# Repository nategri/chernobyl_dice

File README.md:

# Chernobyl Dice

<p align="center"><i>In this clip the Chernobyl Dice set to continuously generate numbers in the range [1,26]. You
can check out a longer YouTube clip showing various modes of here: https://youtu.be/8uue9Aae9ss</i></p>

## Introduction

#### Description

The Chernobyl Dice is a quantum random number generator [0] that uses nuclear decays from a weakly radioactive sample
as a source of entropy. It consists of four primary components:

* An Arduino Nano microcontroller
* A Geiger counter
* Six uranium glass marbles
* Nixie tube display

Geiger counter events ("clicks") are converted into random bits using the following algorithm:

1. In a ring buffer, for each millisecond record either a 0 or a 1, depending on whether or not a Geiger event occurred
2. Perform an initial de-bias of this 0-dominated stream using von Neumann's method [0]
3. Further de-bias by XOR-ing bits generated in the previous step with the mod2 of elapsed 4 microsecond intervals since
since the device was powered on

The uranium glass sample is illuminated by an array of ultraviolet LEDs at each Geiger event, which makes them
fluoresce bright green. This has nothing to do with the radioactivity of the sample, but it does, however, *look
really cool*.

#### Operation

The device has three modes of operations, which can be selected via the rotary switch:

*Clock Mode*

Displays the current time, with the Geiger board unpowered. The time can be set by flipping the toggle switches on and off
(the '16' toggle increments the hour, the '8' toggle increments 10 minutes, the '4' toggle increments 1 minute, and the
'1' toggle resets the seconds).

*Streaming Mode*

Repeatedly generates random numbers of a size specified by the toggles (or random bytes from 0-255 if no toggles are set). Numbers
generated in this mode are transmitted over serial via USB. This mode also has a "turbo" setting to facilitate statistical testing,
which can be enabled by holding down the pushbutton. When "turbo" is enabled bit generation will be indicated by LEDs in the
display, and the Geiger "clicks" will be silent.

*Dice Mode*

In dice mode random number generation is initiated via the pushbutton, and the size of the random number to be generated is set
by the sum of the toggled switches (no switches are set the device will generate random byte in the range 0-255). Press
once to generate the number, and once again to clear the display. The size of the number to be generated is displayed in
blinking digits.

## Statistical Performance

Further testing is required to confirm the consistency of results, but currently the Chernobyl Dice is capable of generating a
1.5+ megabit file that passes [a Python implementation](https://github.com/dj-on-github/sp800_22_tests) of the NIST statistical
test suite [1]. This means the Chernolbyl Dice is likely a *very* fair dice.

```
SUMMARY
-------
monobit_test                             0.279698915238     PASS
frequency_within_block_test              0.404035783453     PASS
runs_test                                0.0688862287393    PASS
longest_run_ones_in_a_block_test         0.959135200804     PASS
binary_matrix_rank_test                  0.532456847429     PASS
dft_test                                 0.000155432528185  FAIL
non_overlapping_template_matching_test   0.999998184707     PASS
overlapping_template_matching_test       0.55898054206      PASS
maurers_universal_test                   0.224223569722     PASS
linear_complexity_test                   0.672504584189     PASS
serial_test                              0.424389760139     PASS
approximate_entropy_test                 0.425255814114     PASS
cumulative_sums_test                     0.348500456103     PASS
random_excursion_test                    0.0753308212732    PASS
random_excursion_variant_test            0.207160448911     PASS
```

```
SUMMARY
-------
monobit_test                             0.105735760191     PASS
frequency_within_block_test              0.436487225319     PASS
runs_test                                0.648059641506     PASS
longest_run_ones_in_a_block_test         0.184787158208     PASS
binary_matrix_rank_test                  0.310400523277     PASS
dft_test                                 0.156504142574     PASS
non_overlapping_template_matching_test   1.00000015958      PASS
overlapping_template_matching_test       0.629208901365     PASS
maurers_universal_test                   0.938296605093     PASS
linear_complexity_test                   0.0880093291441    PASS
serial_test                              0.131826155057     PASS
approximate_entropy_test                 0.137234909215     PASS
cumulative_sums_test                     0.112328349057     PASS
random_excursion_test                    0.17207234069      PASS
random_excursion_variant_test            0.299605480729     PASS
```
<p align="center"><i>Statistical test suite results for two 212667 byte random binary sequences ('rand.binary.1' and 'rand.binary.2')
generated by device. EXPERTS NOTE: The last two tests of the first sequence generate the message: 'J too small
(J=181 < 500) for result to be reliable' so these tests may be ignored for that dataset.</i></p>

The directory `statistical_testing` contains some utilities for assessing and gathering data from the device, including sample
random binary data files, `rand.binary.1` and `rand.binary.2`.

## CAD Drawing

A Fusion 360 CAD drawing of the device can be viewed and downloaded at this URL:

https://a360.co/2OeFT1n

Thanks to the following GrabCAD users for their models:
* [Alex](https://grabcad.com/alex-160) (Nixie tube)
* [Mike Smith](https://grabcad.com/mike.smith-208) (Arduino Nano)
* [Dragos Ionescu](https://grabcad.com/dragos.ionescu-2) (Various pin headers)

## Overview and Parts List

*WARNING: These instructions and resources are not polished and are somewhat untested. This is a project for advanced makers, and
you should fully expect to have a bit of an adventure while building your own Chernobyl Dice! That said: Shoot me a message if
you run into trouble, and I'll try to help you out and improve the instructions as well.*

Here's a rough outline of the steps required for assembly:

1. Print or fabricate the following custom parts from files in the GitHub repository
    * Enclosure (using 3D printer or 3D printing service)
    * Logic, Nixie Display, and Control Panel Custom PCBs (using a board fabrication service such as OSHPark)
    * Stainless steel front panel (using a service such as OSHCut)
    * Acrylic back panel (using a service such as Sculpeo)
2. Order other components (see URLs in the parts list)
3. Embed brass standoffs into enclosure (this is how front and back panels and custom PCBs will be mounted)
    * TIPS
      * A single drop of cyanocrylate (superglue) should be placed in the standoff holes in the enclosure before they are pressed
        in (the tip of a Phillips head screw driver works well for this task)
      * If the tops some holes came out of the printer a bit distorted then they can be widened easily by twisting a largish
        Phillips head screwdriver in them until the top of the hole is wide enough.

4. Assemble custom PCBs and 'exixe' nixie tube driver boards using build photos as a guide
    * TIPS
      * The female headers on the Nixie Display Board for the nixie tube driver PCBs can be assembled using only four long female
        header strips (e.g. there's no need to separately attach sixteen 7-pin female headers---see photos)
      * The "CS" 8-pin male header is a currently a tight fit, so you will probably need to use needle noise pliers to push the pins
        through the board
      * For the control panel PCB you can temporarily mount the toggle switches in the front panel and then press the PCB on top of
        the back of the switches to ensure good alignment---you can then pull the whole board-and-toggle assembly off of the front
        panel to solder it, or even solder it in place and then pull it off
      * The file 'nixie_holder.stl' is a provided as a useful place to rest the nixie tube while soldering them to the 'exixe' driver
        boards
5. Attach the acrylic back panel and panel mount USB cable to the rear of the enclosure
6. Mount custom PCBs inside enclosure and perform wiring (see wiring schematic and build photos)
7. Partially dis-assemble rotary switch to attach it to the "lock plate" (lock_plate.stl)
8. Perform any necessary finishing to the stainless steel front panel
    * TIPS
      * Some mounting holes for toggles and switches may need to be widened (use a round file for this)
      * Surface finish of a laser cut part can be improved by sanding *with the grain* using ~300 grit sandpaper (test on the back
        side first)
9. Mount toggle-and-PCB assembly, LED-with-holder assemblies, rotary-switch-and-lock-plate assembly, and pushbutton on front panel
    * TIP
      * While attaching the LED to the holder, apply a drop of cyanocrylate (superglue) to prevent the LED from falling out of the
        front of the holder
10. Perform wiring of the control panel (see wiring schematic and build photos)
11. Fit the eight nixie display driver boards into the female headers of the Nixie Display Board
12. Wire the Control Panel to the Logic Board
13. Mount the front panel to the enclosure, taking care to insure that the hole in the rotary switch lock plate lines up with the
    upper-left standoff on the front of the radioactive sample holder

**Standoff Size Guide**

| Location | Standoff Length | Type |
| --- | --- | --- |
| Rear of enclosure | 10 mm | Female-Female |
| Front of enclosure | 10 mm | Female-Female |
| Nixie Display Board mount | 40 mm | Female-Female |
| Logic Board mount | 20 mm | Female-Female|
| Logic Board-to-Geiger Board | 30 mm | Male-Female |
| Geiger Board-to-Bottom of Uranium Sample Box | 15 mm | Male-Female |
| Bottom of Uranium Sample Box-to-Top of Uranium Sample Box | 6 mm | Male-Female |
| Top of Uranium Sample Box-to-Front Panel | 6 mm | Male-Female |

NOTE: For large internal standoff distances (e.g. the Nixie Display mount) two standoffs can be stacked to achieve
the desired distance.

## Wiring Diagram

<p align="center"><i>How connect the internal wiring of the Chernobyl Dice.</i></p>

## Build Photos

**Enclosure with Standoffs Inserted**

<p align="center"><i>
You can ignore the white breadboards on the left of the enclosure. These assisted in an earlier iteration of the
project and are not needed for assembly.
<a href="https://raw.githubusercontent.com/nategri/chernobyl_dice/master/images/build/large/1.JPG">Click here</a>
for larger photo.
</i></p>

<br><br><br>

**Logic Board Mounted**

<p align="center"><i>
Note the wires for UV LED array are run beneath the logic board.
<a href="https://raw.githubusercontent.com/nategri/chernobyl_dice/master/images/build/large/2.JPG">Click here</a>
for larger photo.
</i></p>

<br><br><br>

**Nixie Display Board Wiring**

<p align="center"><i>
<a href="https://raw.githubusercontent.com/nategri/chernobyl_dice/master/images/build/large/3.JPG">Click here</a>
for larger photo.
</i></p>

<br><br><br>

**Nixie Display Board Mounted and Logic Board Wiring**

<p align="center"><i>
<a href="https://raw.githubusercontent.com/nategri/chernobyl_dice/master/images/build/large/4.JPG">Click here</a>
for larger photo.
</i></p>

<br><br><br>

**Geiger Board Mounted**

<p align="center"><i>
NOTE: You must pull the JMP2 jumper near the center of the Geiger board (this turns off the built-in speaker of the
board---we want these clicks to be optional and controlled by firmware instead).
<a href="https://raw.githubusercontent.com/nategri/chernobyl_dice/master/images/build/large/5.JPG">Click here</a>
for larger photo.
</i></p>

<br><br><br>

**Uranium Sample Holder Lower Half Detail**

<p align="center"><i>
UV LEDs and piezo speaker are glued mounted into place using cyanocrylate (superglue) adhesive. Uranium glass
marbles will be held in place mechanically when the top half is mounted.
<a href="https://raw.githubusercontent.com/nategri/chernobyl_dice/master/images/build/large/6.JPG">Click here</a>
for larger photo.
</i></p>

<br><br><br>

**Uranium Sample Holder Lower Half Mounted**

<p align="center"><i>
The middle standoff is attached on the underside with a nut.
<a href="https://raw.githubusercontent.com/nategri/chernobyl_dice/master/images/build/large/7.JPG">Click here</a>
for larger photo.
</i></p>

<br><br><br>

**Uranium Sample Holder Top Half Mounted**

<p align="center"><i>
<a href="https://raw.githubusercontent.com/nategri/chernobyl_dice/master/images/build/large/8.JPG">Click here</a>
for larger photo.
</i></p>

<br><br><br>

**Control Panel Board Wired**

<p align="center"><i>
<a href="https://raw.githubusercontent.com/nategri/chernobyl_dice/master/images/build/large/9.JPG">Click here</a>
for larger photo.
</i></p>

<br><br><br>

**Control Panel Board Wiring Detail**

<p align="center"><i>
<a href="https://raw.githubusercontent.com/nategri/chernobyl_dice/master/images/build/large/10.JPG">Click here</a>
for larger photo.
</i></p>

## Acknowledgements

Many thanks to Emily Velasco ([@MLE_Online](https://twitter.com/MLE_Online)) for advice on stainless steel surface sanding,
and for generally being enthusiastic as heck about this project.

## References

[0] "Quantum Random Number Generators." M. Herrero-Collantes and J. C. Garcia-Escartin.
https://arxiv.org/abs/1604.03304

[1] "A Statistical Test Suite for Random and Pseudorandom Number Generators for Cryptographic Applications."
https://csrc.nist.gov/publications/detail/sp/800-22/rev-1a/final

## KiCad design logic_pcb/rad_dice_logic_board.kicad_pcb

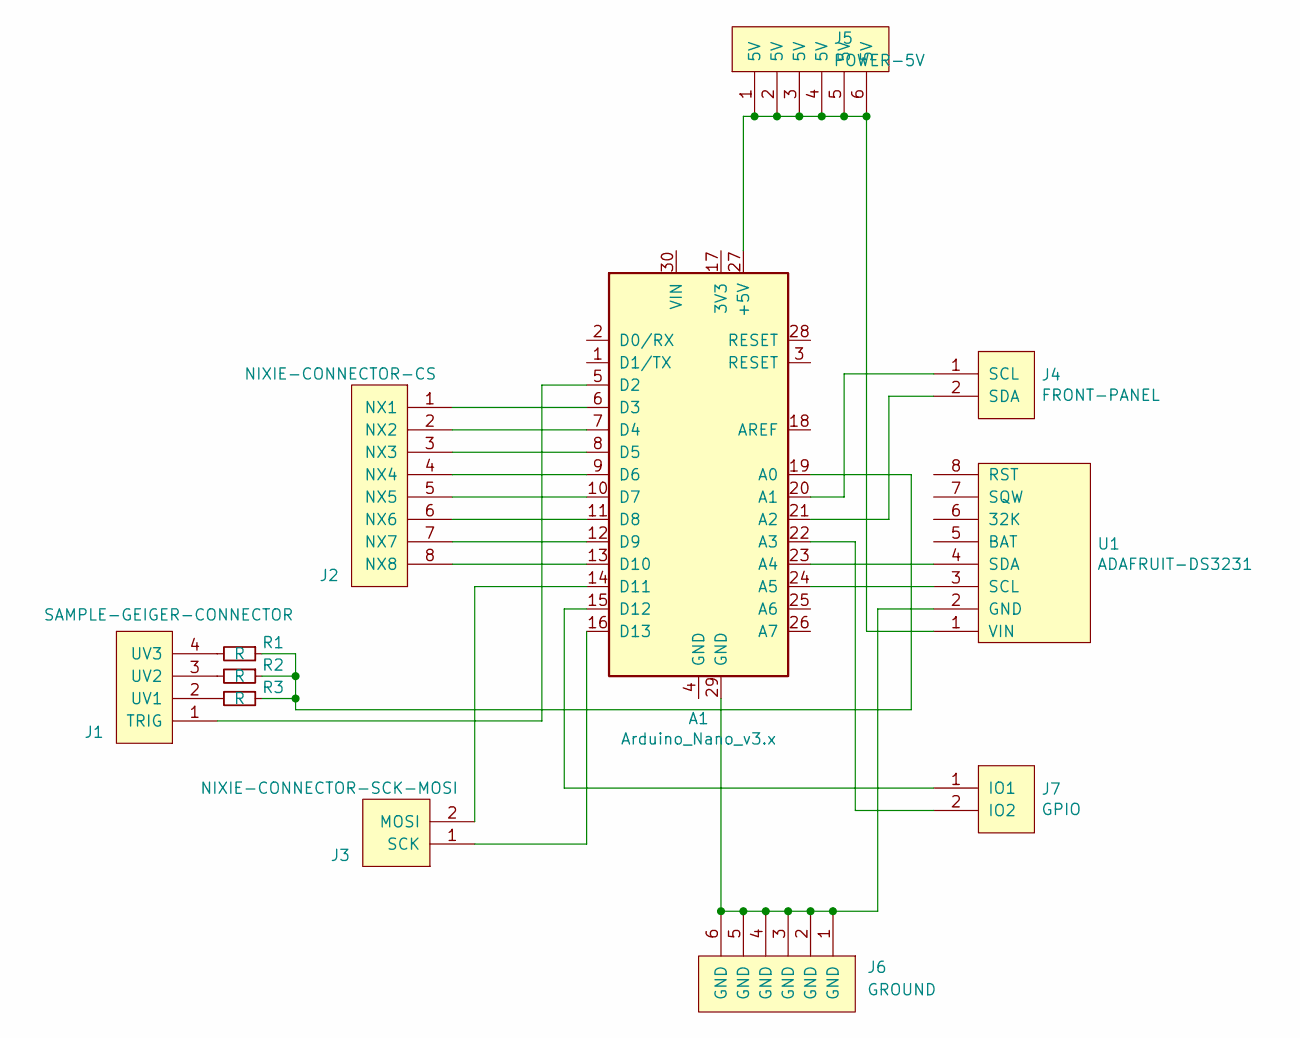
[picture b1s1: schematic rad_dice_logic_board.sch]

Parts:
A1: Arduino_Nano_v3.x; Arduino_Nano
J1: SAMPLE-GEIGER-CONNECTOR; Pin_Header_Angled_1x04_Pitch2.54mm
J2: NIXIE-CONNECTOR-CS; Pin_Header_Angled_1x08_Pitch2.54mm
J3: NIXIE-CONNECTOR-SCK-MOSI; Pin_Header_Angled_1x02_Pitch2.54mm
J4: FRONT-PANEL; Pin_Header_Angled_1x02_Pitch2.54mm
J5: POWER-5V; Pin_Header_Angled_1x06_Pitch2.54mm
J6: GROUND; Pin_Header_Angled_1x06_Pitch2.54mm
J7: GPIO; Pin_Header_Angled_1x02_Pitch2.54mm
R1, R2, R3: R; R_Axial_DIN0207_L6.3mm_D2.5mm_P10.16mm_Horizontal
U1: ADAFRUIT-DS3231

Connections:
unnamed: A1.5 (D2), J1.1 (TRIG)
unnamed: A1.6 (D3), J2.1 (NX1)
unnamed: A1.7 (D4), J2.2 (NX2)
unnamed: A1.8 (D5), J2.3 (NX3)
unnamed: A1.9 (D6), J2.4 (NX4)
unnamed: A1.10 (D7), J2.5 (NX5)
unnamed: A1.11 (D8), J2.6 (NX6)
unnamed: A1.12 (D9), J2.7 (NX7)
unnamed: A1.13 (D10), J2.8 (NX8)
unnamed: A1.14 (D11), J3.2 (MOSI)
unnamed: A1.15 (D12), J7.1 (IO1)
unnamed: A1.16 (D13), J3.1 (SCK)
unnamed: A1.19 (A0), R1.1, R2.1, R3.1
unnamed: A1.20 (A1), J4.1 (SCL)
unnamed: A1.21 (A2), J4.2 (SDA)
unnamed: A1.22 (A3), J7.2 (IO2)
unnamed: A1.23 (A4), U1.4 (SDA)
unnamed: A1.24 (A5), U1.3 (SCL)
unnamed: A1.27 (+5V), J5.1, J5.2, J5.3, J5.4, J5.5, J5.6, U1.1 (VIN)
unnamed: A1.29 (GND), J6.1, J6.2, J6.3, J6.4, J6.5, J6.6, U1.2 (GND)
unnamed: J1.2 (UV1), R3.2
unnamed: J1.3 (UV2), R2.2
unnamed: J1.4 (UV3), R1.2

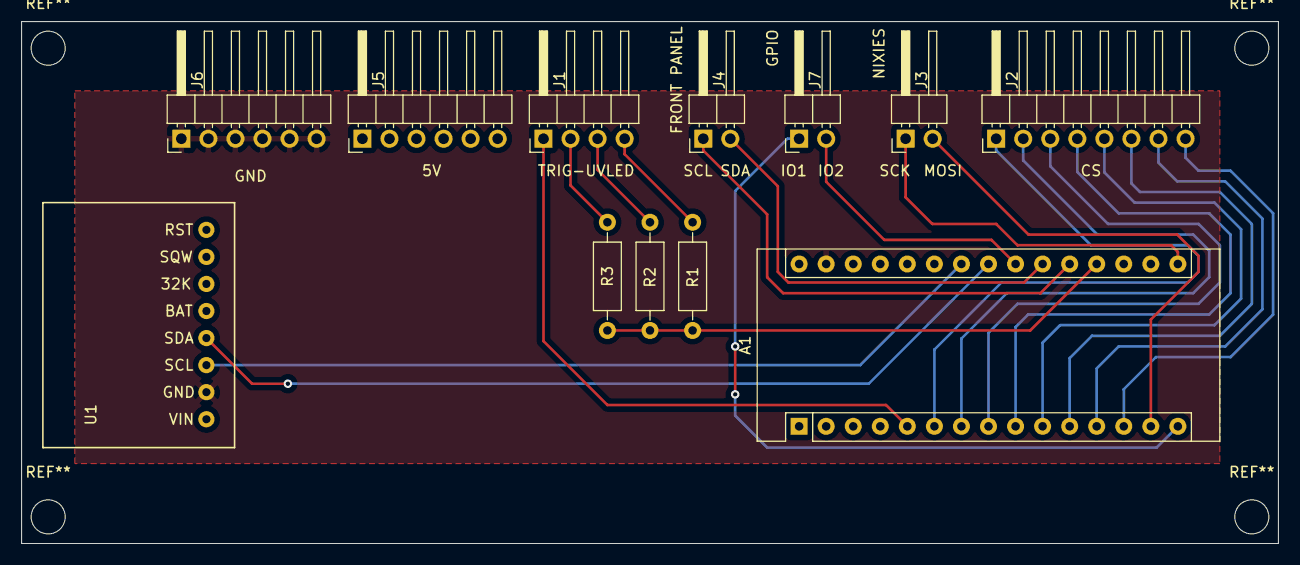
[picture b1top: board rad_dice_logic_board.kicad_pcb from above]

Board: 2 copper layers, 118.0 x 49.0 mm, 12 parts (0 on the bottom side), 23 nets.

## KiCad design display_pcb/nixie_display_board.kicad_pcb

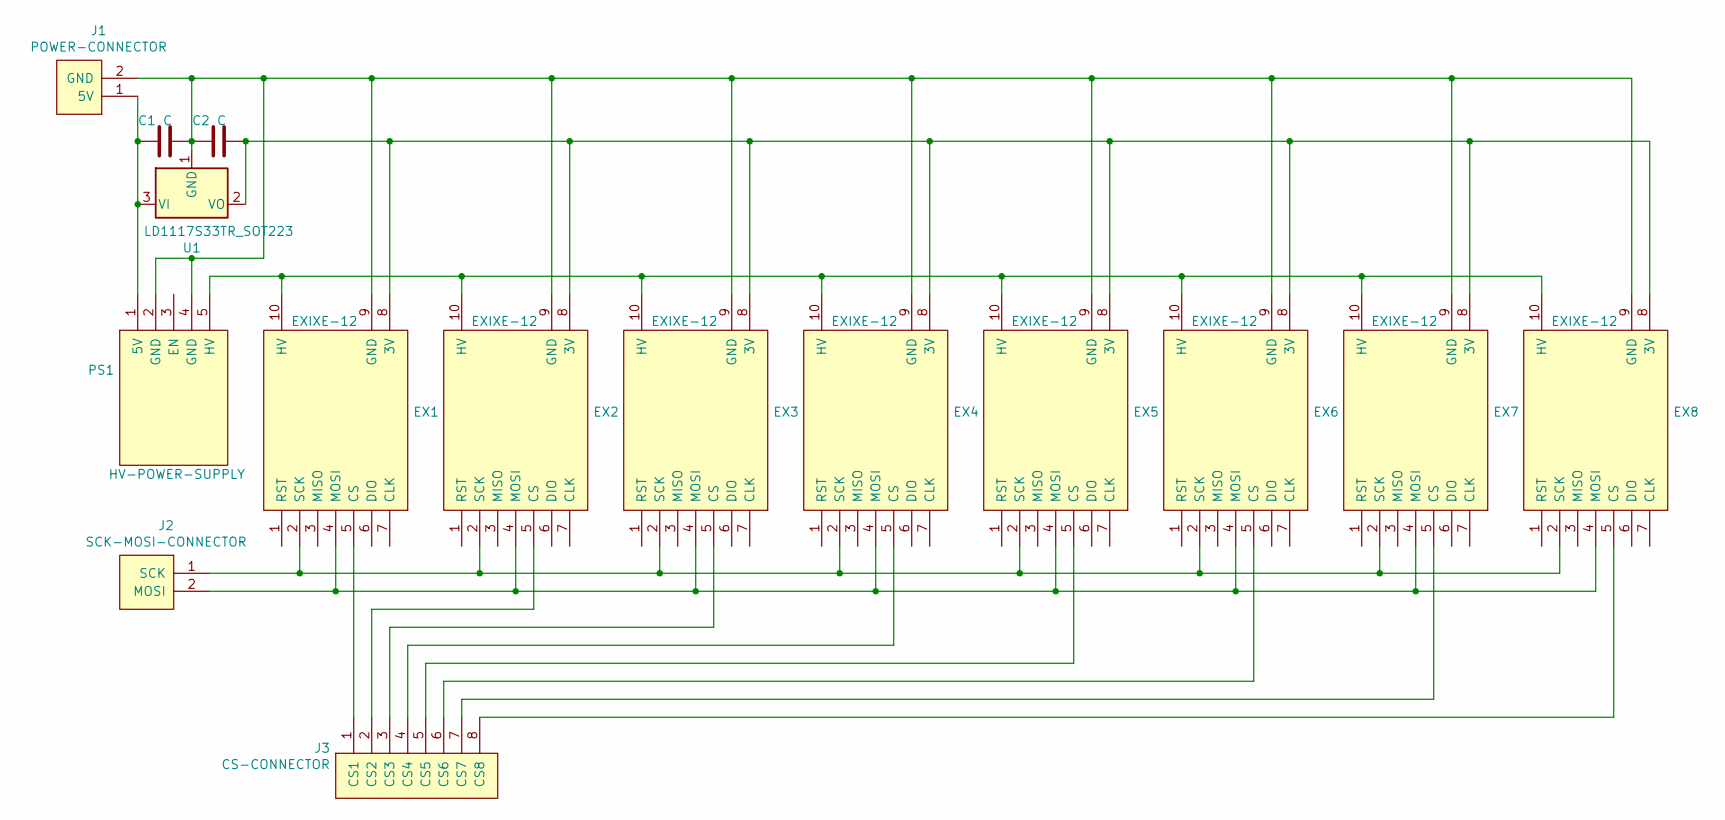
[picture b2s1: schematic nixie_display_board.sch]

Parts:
C1, C2: C; C_Disc_D6.0mm_W2.5mm_P5.00mm
EX1, EX2, EX3, EX4, EX5, EX6, EX7, EX8: EXIXE-12; exixe-12-board
J1: POWER-CONNECTOR; power-connector
J2: SCK-MOSI-CONNECTOR; sck-mosi-connector
J3: CS-CONNECTOR; cs-connector
PS1: HV-POWER-SUPPLY; hv-power-supply
U1: LD1117S33TR_SOT223; TO-220-3_Vertical

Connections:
unnamed: C1.1, J1.1 (5V), PS1.1 (5V), U1.3 (VI)
unnamed: C1.2, C2.1, EX1.9 (GND), EX2.9 (GND), EX3.9 (GND), EX4.9 (GND), EX5.9 (GND), EX6.9 (GND), EX7.9 (GND), EX8.9 (GND), J1.2 (GND), PS1.2 (GND), PS1.4 (GND), U1.1 (GND)
unnamed: C2.2, EX1.8 (3V), EX2.8 (3V), EX3.8 (3V), EX4.8 (3V), EX5.8 (3V), EX6.8 (3V), EX7.8 (3V), EX8.8 (3V), U1.2 (VO)
unnamed: EX1.2 (SCK), EX2.2 (SCK), EX3.2 (SCK), EX4.2 (SCK), EX5.2 (SCK), EX6.2 (SCK), EX7.2 (SCK), EX8.2 (SCK), J2.1 (SCK)
unnamed: EX1.4 (MOSI), EX2.4 (MOSI), EX3.4 (MOSI), EX4.4 (MOSI), EX5.4 (MOSI), EX6.4 (MOSI), EX7.4 (MOSI), EX8.4 (MOSI), J2.2 (MOSI)
unnamed: EX1.5 (CS), J3.1 (CS1)
unnamed: EX1.10 (HV), EX2.10 (HV), EX3.10 (HV), EX4.10 (HV), EX5.10 (HV), EX6.10 (HV), EX7.10 (HV), EX8.10 (HV), PS1.5 (HV)
unnamed: EX2.5 (CS), J3.2 (CS2)
unnamed: EX3.5 (CS), J3.3 (CS3)
unnamed: EX4.5 (CS), J3.4 (CS4)
unnamed: EX5.5 (CS), J3.5 (CS5)
unnamed: EX6.5 (CS), J3.6 (CS6)
unnamed: EX7.5 (CS), J3.7 (CS7)
unnamed: EX8.5 (CS), J3.8 (CS8)

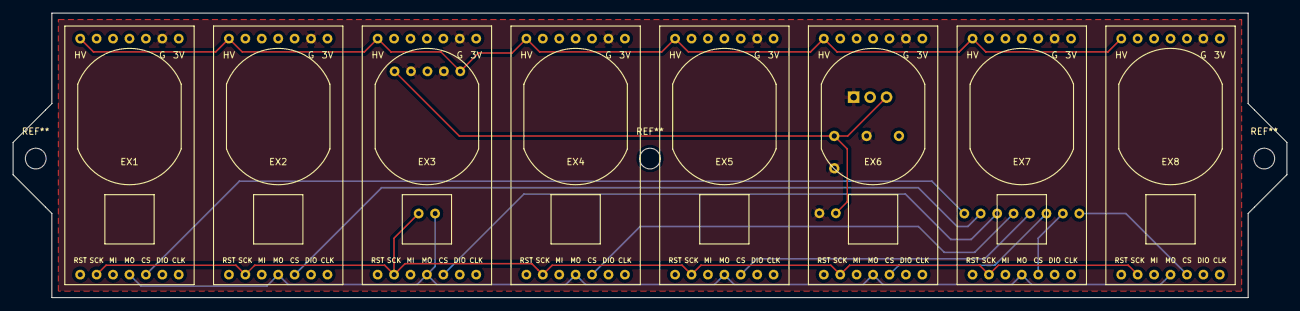
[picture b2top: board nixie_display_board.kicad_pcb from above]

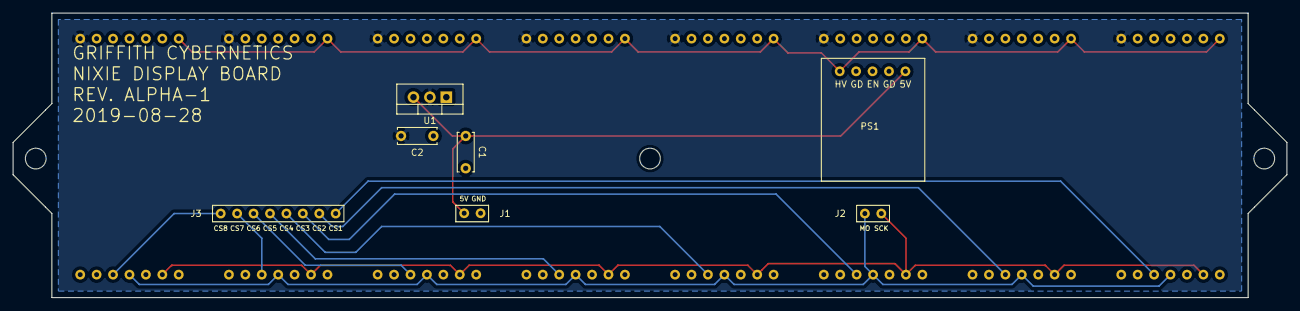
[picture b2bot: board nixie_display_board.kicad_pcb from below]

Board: 2 copper layers, 197.0 x 44.0 mm, 15 parts (7 on the bottom side), 14 nets.

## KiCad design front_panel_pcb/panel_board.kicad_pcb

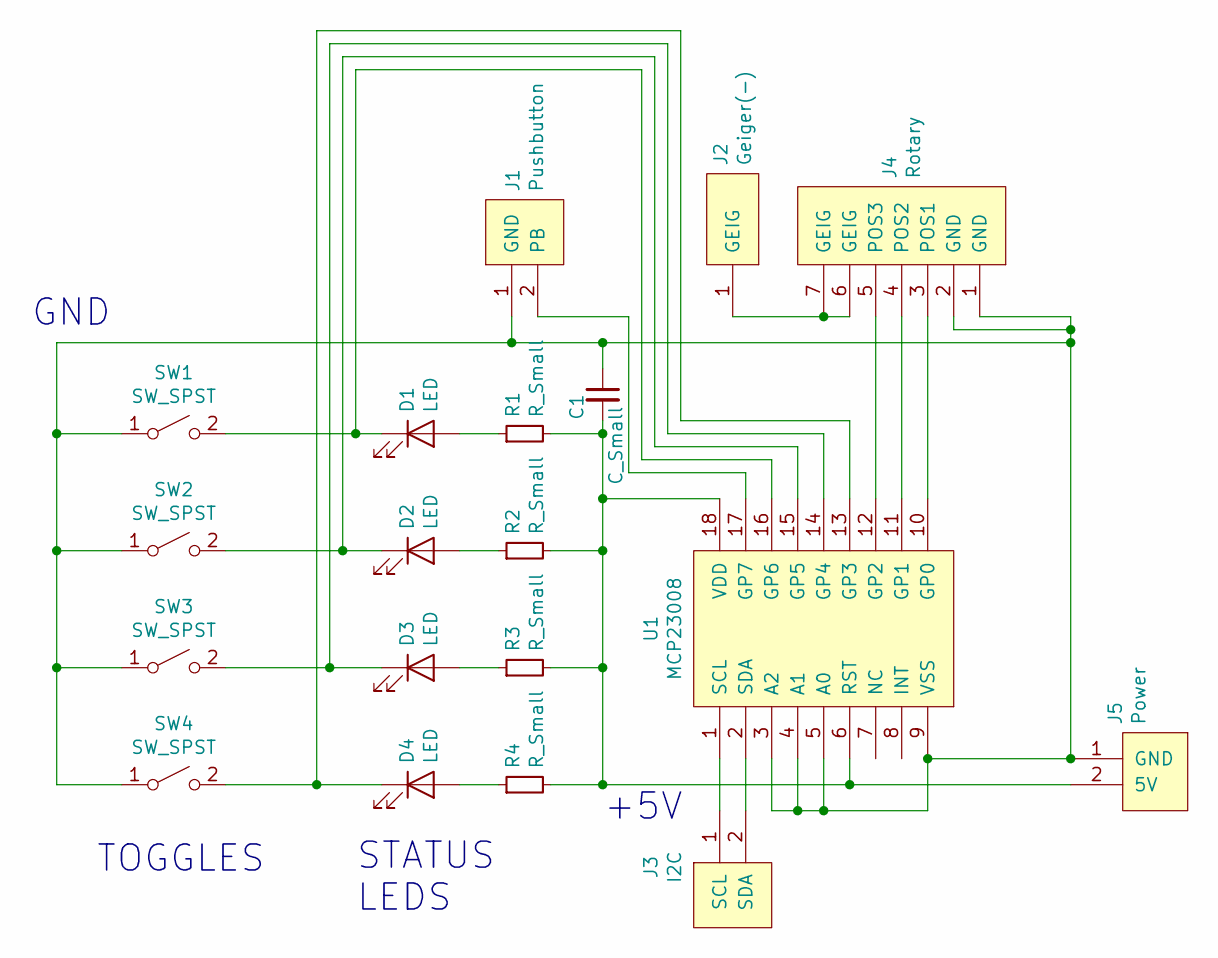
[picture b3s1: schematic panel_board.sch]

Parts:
C1: C_Small; C_Disc_D6.0mm_W2.5mm_P5.00mm
D1, D2, D3, D4: LED; Pin_Header_Straight_1x02_Pitch2.54mm
J1: Pushbutton; Pin_Header_Straight_1x02_Pitch2.54mm
J2: Geiger(-); Pin_Header_Straight_1x01_Pitch2.54mm
J3: I2C; Pin_Header_Straight_1x02_Pitch2.54mm
J4: Rotary; Pin_Header_Straight_1x07_Pitch2.54mm
J5: Power; Pin_Header_Straight_1x02_Pitch2.54mm
R1, R2, R3, R4: R_Small; R_Axial_DIN0207_L6.3mm_D2.5mm_P10.16mm_Horizontal
SW1, SW2, SW3, SW4: SW_SPST; ToggleSW
U1: MCP23008; DIP-18_W7.62mm_Socket

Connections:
unnamed: C1.1, J1.1 (GND), J4.1 (GND), J4.2 (GND), J5.1 (GND), SW1.1 (A), SW2.1 (A), SW3.1 (A), SW4.1 (A), U1.3 (A2), U1.4 (A1), U1.5 (A0), U1.9 (VSS)
unnamed: C1.2, J5.2 (5V), R1.2, R2.2, R3.2, R4.2, U1.6 (RST), U1.18 (VDD)
unnamed: D1.1 (K), SW1.2 (B), U1.16 (GP6)
unnamed: D1.2 (A), R1.1
unnamed: D2.1 (K), SW2.2 (B), U1.15 (GP5)
unnamed: D2.2 (A), R2.1
unnamed: D3.1 (K), SW3.2 (B), U1.14 (GP4)
unnamed: D3.2 (A), R3.1
unnamed: D4.1 (K), SW4.2 (B), U1.13 (GP3)
unnamed: D4.2 (A), R4.1
unnamed: J1.2 (PB), U1.17 (GP7)
unnamed: J2.1, J4.6 (GEIG), J4.7 (GEIG)
unnamed: J3.1 (SCL), U1.1 (SCL)
unnamed: J3.2 (SDA), U1.2 (SDA)
unnamed: J4.3 (POS1), U1.10 (GP0)
unnamed: J4.4 (POS2), U1.11 (GP1)
unnamed: J4.5 (POS3), U1.12 (GP2)

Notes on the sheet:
+5V
GND
STATUS LEDS
TOGGLES

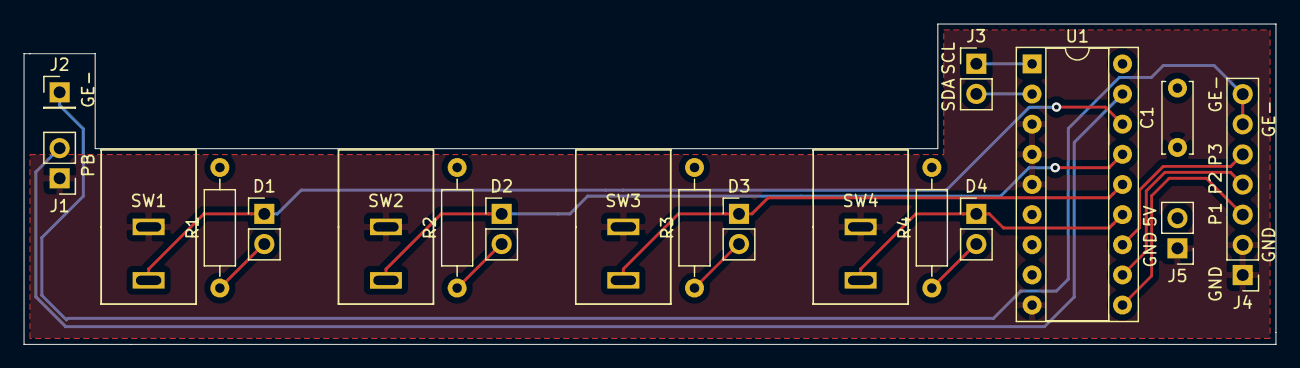
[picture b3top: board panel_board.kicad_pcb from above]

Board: 2 copper layers, 105.5 x 27.0 mm, 19 parts (0 on the bottom side), 17 nets.

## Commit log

2019-07-27 use time-window/von neuman approach
2019-07-28 dont use RLE on the ring buffer
2019-08-10 add delay to allow ring buffer to move forward
2019-09-01 added stuff for nixies/switches---still need to remove bias from dice mode
2019-09-01 dice de-biased
2019-09-05 off button for clock display; dice mode bug fix
2019-09-07 add pcb files and rename firmware
2019-09-07 update logic board for compatibility with front panel board
2019-09-08 add turbo mode to streaming
2019-09-13 ring buffer doesnt need to be an unsigned long, FFS
2019-09-13 add dependecies as files
2019-09-13 moved nixie interface to separate files
2019-09-15 updated for control panel pcb
2019-09-17 add parts list file (wip)
2019-09-17 add title to parts list
2019-09-17 fix table?
2019-09-17 add much more to parts list
2019-09-17 tweak nixie led mode color
2019-09-19 attempt to set style
2019-09-22 fix gnd/5v bug and add 2 gpio pins
2019-10-03 change format of parts list; add parts directory and associated files
2019-10-24 changes associated with adding software controlled speaker
2019-10-24 fix small issues so code will compile
2019-10-26 correct order of nixie tubes and increase spi freq
2019-10-27 add routines for setting the clock
2019-10-27 increase baudrate on serial
2019-11-06 add images of construction
2019-11-06 different directories for large and small build images
2019-11-06 make small images smaller
2019-11-07 add wiring schematic
2019-11-12 add image of device
2019-11-12 add readme file
2019-11-12 add title
2019-11-12 add wiring diagram to readme
2019-11-12 save changes in readme
2019-11-18 attempt to add extra de-biasing step
2019-11-20 debug previous commit related to extra de-bias step
2019-11-24 add rough instructions to overview
2019-11-25 add table for standoff sizes
2019-11-25 move table and add title
2019-11-25 correct titles
2019-11-25 fix title
2019-12-03 documentation progress
2019-12-03 fix parts list table
2019-12-03 fix links and add build photo titles
2019-12-03 fix titles
2019-12-03 add more caption info to build photos
2019-12-04 add nixie holder and update parts list to include sample holder
2019-12-04 fix parts list
2019-12-05 promising statistical results in firmware
2019-12-05 remove code that had been commented out
2019-12-05 add remainder of parts files
2019-12-08 add statistical testing directory
2019-12-08 revert firmware to von neumann methode approach
2019-12-16 update README with new algo details
2019-12-16 update stat test section
2019-12-18 fix spelling mistakes
2019-12-18 fix one typo
2019-12-20 add extra de-biasing
2019-12-21 update README with test results and add sample data files
2019-12-21 add animated gif
2019-12-21 add description to gif
2019-12-21 fix link in gif description
2019-12-21 added MIT license
2019-12-21 add correct youtube link
2019-12-22 detail to algo description
2019-12-22 improve algo description
